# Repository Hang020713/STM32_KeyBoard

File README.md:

# STM32_KeyBoard
A repo for storing detail of making STM32 KeyBoard

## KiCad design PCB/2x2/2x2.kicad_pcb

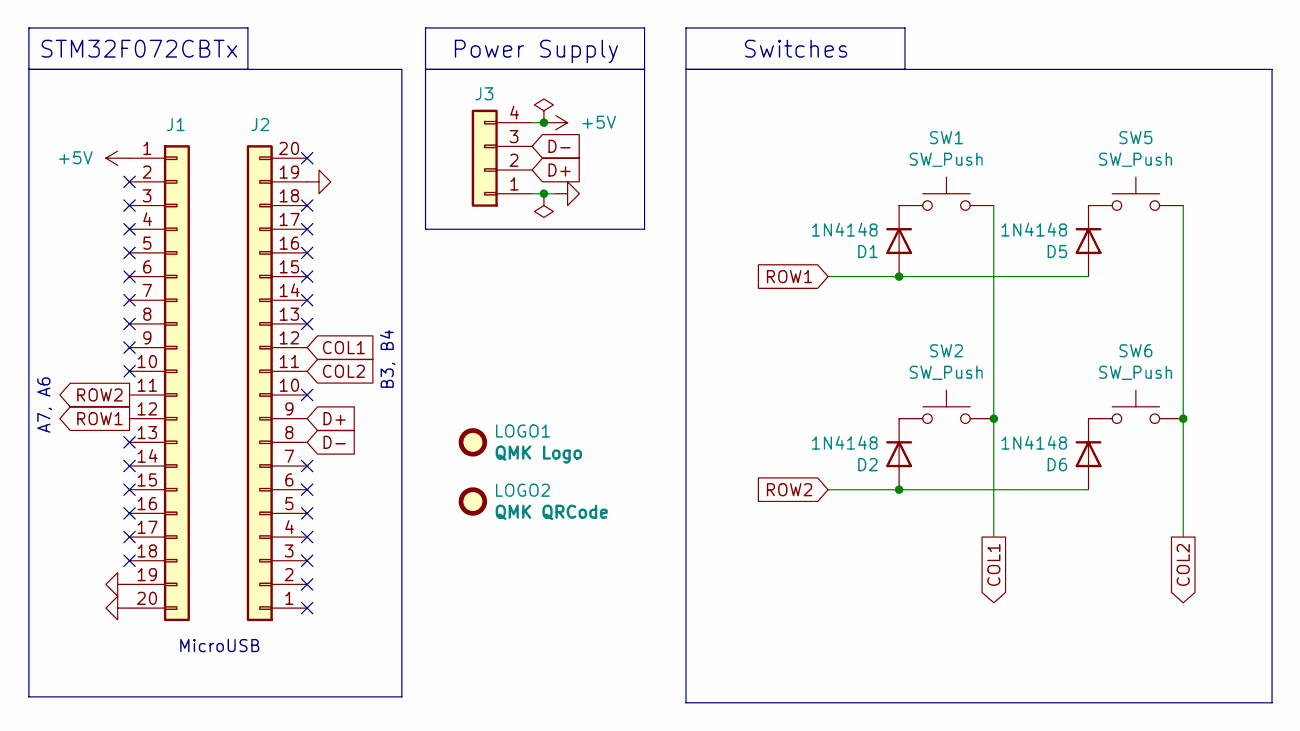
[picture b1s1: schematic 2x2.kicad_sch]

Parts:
D1, D2, D5, D6: 1N4148; D_SOD-323
J1, J2: Conn_01x20; PinHeader_1x20_P2.54mm_Vertical
J3: Conn_01x04; PinHeader_1x04_P2.54mm_Vertical
LOGO1: QMK Logo; QMK_PoweredBy
LOGO2: QMK QRCode; QMK_QRCode_0.4mm
SW1, SW2, SW5, SW6: SW_Push; Kailh_socket_MX

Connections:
+5V: J1.1, J3.4
COL1: J2.12, SW1.2, SW2.2
COL2: J2.11, SW5.2, SW6.2
D+: J2.9, J3.2
D-: J2.8, J3.3
GND: J1.19, J1.20, J2.19, J3.1
unnamed: D1.1 (K), SW1.1
unnamed: D2.1 (K), SW2.1
unnamed: D5.1 (K), SW5.1
unnamed: D6.1 (K), SW6.1
ROW1: D1.2 (A), D5.2 (A), J1.12
ROW2: D2.2 (A), D6.2 (A), J1.11

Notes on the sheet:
Power Supply
B3, B4
Switches
STM32F072CBTx
MicroUSB
A7, A6

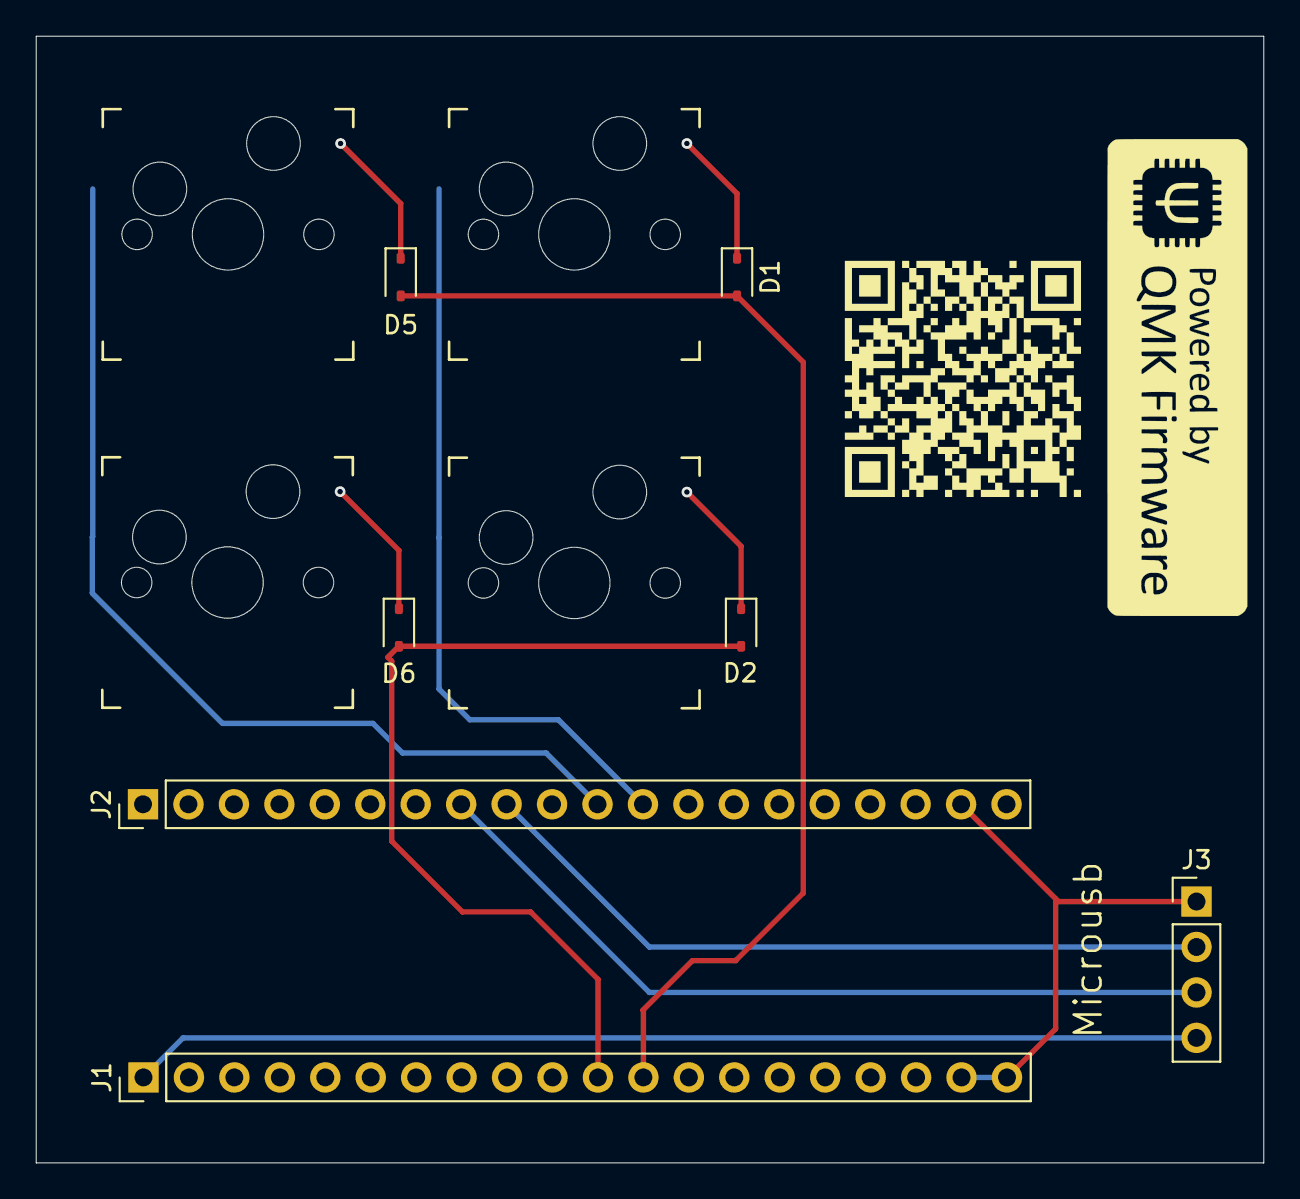
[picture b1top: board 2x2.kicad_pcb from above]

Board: 2 copper layers, 68.6 x 63.0 mm, 13 parts (0 on the bottom side), 12 nets.

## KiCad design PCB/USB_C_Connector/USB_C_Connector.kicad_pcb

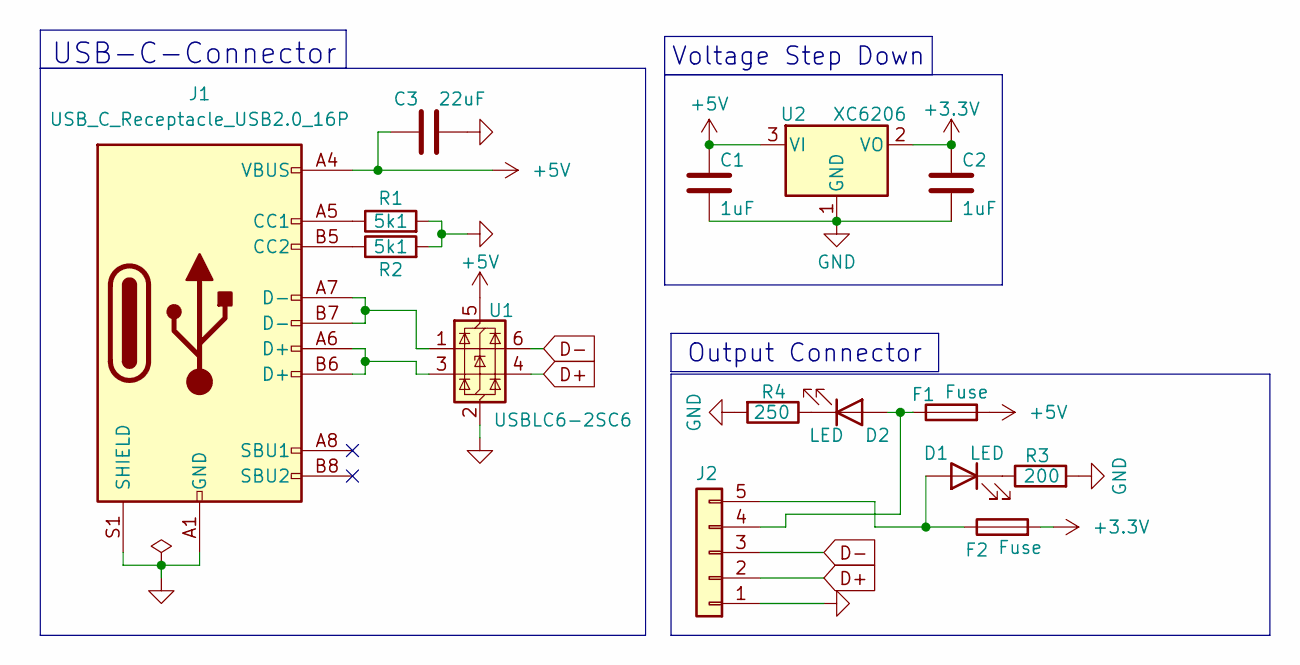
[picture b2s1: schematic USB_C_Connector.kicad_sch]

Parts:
C1, C2: 1uF; C_0603_1608Metric_Pad1.08x0.95mm_HandSolder
C3: 22uF; C_0603_1608Metric_Pad1.08x0.95mm_HandSolder
D1, D2: LED; LED_0805_2012Metric
F1, F2: Fuse; Fuse_0603_1608Metric_Pad1.05x0.95mm_HandSolder
J1: USB_C_Receptacle_USB2.0_16P; USB_C_Receptacle_HRO_TYPE-C-31-M-12
J2: Conn_01x05; PinHeader_1x05_P2.54mm_Vertical
R1, R2: 5k1; R_0603_1608Metric_Pad0.98x0.95mm_HandSolder
R3: 200; R_0603_1608Metric_Pad0.98x0.95mm_HandSolder
R4: 250; R_0603_1608Metric_Pad0.98x0.95mm_HandSolder
U1: USBLC6-2SC6; SOT-23-6
U2: XC6206; SOT-23-3

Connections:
+3.3V: C2.1, F2.2, U2.2 (VO)
+5V: C1.1, C3.1, F1.2, J1.A4 (VBUS), J1.A9 (VBUS), J1.B4 (VBUS), J1.B9 (VBUS), U1.5 (VBUS), U2.3 (VI)
D+: J2.2, U1.4 (I/O2)
D-: J2.3, U1.6 (I/O1)
GND: C1.2, C2.2, C3.2, J1.A1 (GND), J1.A12 (GND), J1.B1 (GND), J1.B12 (GND), J1.S1 (SHIELD), J2.1, R1.2, R2.2, R3.2, R4.2, U1.2 (GND), U2.1 (GND)
unnamed: D1.2 (A), F2.1, J2.5
unnamed: D1.1 (K), R3.1
unnamed: D2.2 (A), F1.1, J2.4
unnamed: D2.1 (K), R4.1
unnamed: J1.A5 (CC1), R1.1
unnamed: J1.B5 (CC2), R2.1
unnamed: J1.A6 (D+), J1.B6 (D+), U1.3 (I/O2)
unnamed: J1.A7 (D-), J1.B7 (D-), U1.1 (I/O1)

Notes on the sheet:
USB-C-Connector
Voltage Step Down
Output Connector

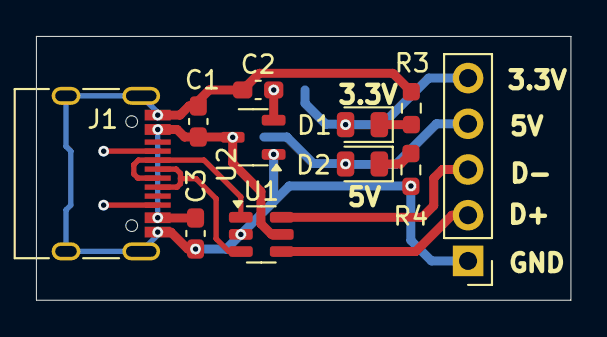
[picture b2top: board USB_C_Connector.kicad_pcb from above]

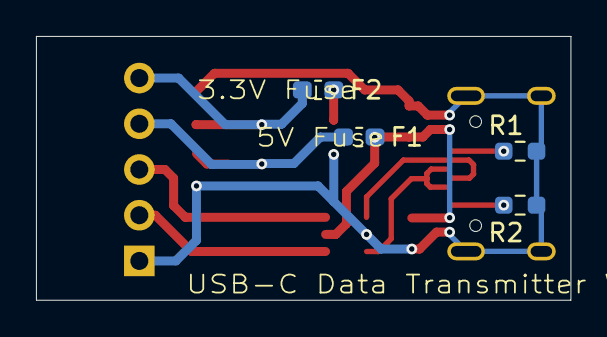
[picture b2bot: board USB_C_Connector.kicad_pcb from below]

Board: 2 copper layers, 29.7 x 14.7 mm, 15 parts (4 on the bottom side), 13 nets.

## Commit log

2025-06-08 Create KiCad files
2025-06-10 Update PCB
2025-06-15 add vial_qmk
2025-06-15 Add many things
2025-06-15 Update 2x2
2025-06-15 minor stuff
